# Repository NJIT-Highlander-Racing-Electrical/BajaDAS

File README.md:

# BajaDAS: Readme and Quickstart Guide

## PlatformIO 

1. Software Dependencies:
   - `Visual Studio Code` with `PlatformIO IDE` extension
   - `Git` (if editing)
   - `GitHub Desktop App` (recommended for repository organization)
4. Clone the repository and open the project. If PlatformIO IDE is installed, it should recognize the project and automatically initialize the extension.

## Quick Start

1. Insert a formatted `MicroSD` card into the BajaDAS system.
2. Open the project folder in `Visual Studio Code`.
3. Use the `PlatformIO: Upload` button to load the code onto the microcontroller.
4. Post-race, retrieve the SD card and access the `.csv` files for analysis.

## Troubleshooting

- The main config file is `platformio.ini`.
- Avoid hotswapping MicroSD cards. While the code is set up to automatically detect a card when inserted, the code is very buggy. Always power cycle the system after inserting a new card.

# About BajaDAS
This project was started in 2023 as the first part of our whole-vehicle data acquisition (DAQ) system. It serves as the central data logger, with a few onboard sensors. It is not, however, required by or special on the CAN system.

## System Capabilities
- Data logging via MicroSD card (data is stored in a .csv file)
- Adafruit Ultimate GPS
- Battery Level Sensing
- IMU

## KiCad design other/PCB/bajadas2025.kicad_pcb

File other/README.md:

# BajaDAS: Data Acquisition System for Highlander Racing

BajaDAS is a data acquisition system tailored for the Highlander Racing team's vehicles. It gathers real-time telemetry data, crucial for performance analytics and diagnostics.

## 2025-2026 Changes to Make

* Incorporate this [Adafruit Panel Mount Micro SD Card Extender](https://www.google.com/aclk?sa=l&ai=DChcSEwjj9bOK6cmKAxXBVEcBHVRjHN4YABASGgJxdQ&ae=2&aspm=1&co=1&ase=5&gclid=Cj0KCQiAvbm7BhC5ARIsAFjwNHsn8yJzOILmMZRqH4E_HPufaiggZcexFWYqg4a0y1KrF-u19AfAwZwaAi_wEALw_wcB&sig=AOD64_018L6tCDBYVmc7ekdmUu69rXhYmw&ctype=5&q=&ved=2ahUKEwjsy62K6cmKAxUiFFkFHVE7BFwQww8oAnoECAYQDA&adurl=) for easier use. This will require a waterproof screw on or press fit cover but will make removing the microSD far easier
     * I think we can also just place a microSD card slot for the other end of that panel mount directly to the PCB. It looks like the "reader" we use now just does some voltage regulation and level shifting, but since the ESP32 already uses 3.3V we may be OK without the additional hardware
     * Update the 3D Model and the PCB accordingly for these changes

* Include external pull-up resistors for any input pins on 34, 35, 36, or 39 since these do not have internal pullups

## Features

- **9-DOF Sensor**: Gathers acceleration, magnetic field, gyroscope, and temperature data via the `Adafruit_LSM9DS1` sensor.
- **GPS Integration**: Records GPS data, specifically latitude, longitude, fix status, and satellite count.
- **SD Card Logging**: Logs data to an SD card in CSV format.
- **Serial Logging**: Outputs sensor readings to the serial console for live monitoring.
- **CAN Bus Support**: Receives all incoming vehicle data using a TJA1051T CAN Transceiver.
- **Connection Modularity**: Screw Terminals on DAQ PCB so that additional modules can be connected to the microcontroller in the future
- **Fuel Sensor**: Integrates the fuel sensor and data storage as a part of the DAS

## Hardware Setup

- **Microcontroller**: Designed for Arduino-compatible boards with multiple hardware serial interfaces and SPI capabilities.
- **SD Card**: MicroSD card slot for data logging. Ensure it's formatted correctly.
- **Sensors**: Adafruit LSM9DS1 9-DOF sensor and a GPS module.

## GPS Information

* GPS System that tracks vehicle location (latitude and longitude) as well as reporting other information like time and date

### GPS Design Goals

* CAN-Bus integration with Adafruit Ultimate GPS module reports latitude, longitude, time, and date
* Active antenna mounted to firewall increases reception

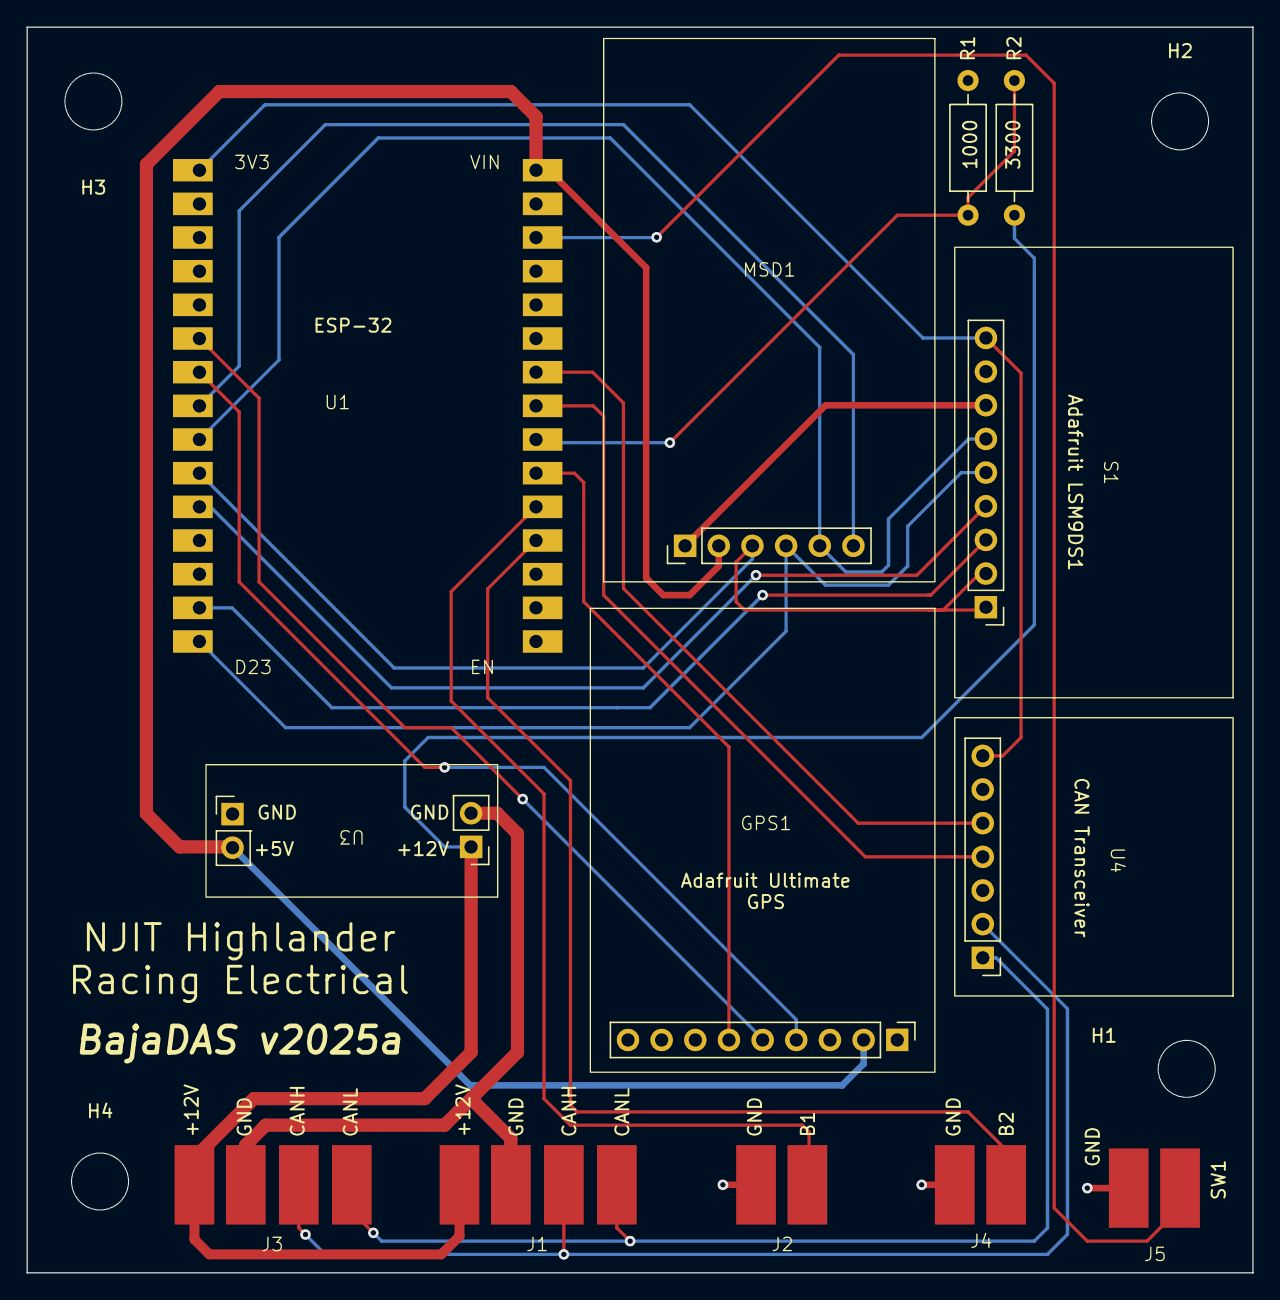
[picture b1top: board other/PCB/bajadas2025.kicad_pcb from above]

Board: 2 copper layers, 92.5 x 94.0 mm, 17 parts (0 on the bottom side), 21 nets.

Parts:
GPS1: Adafruit Ultimate GPS v1
H1, H2, H3, H4: MountingHole; MountingHole_4.3mm_M4
J1: Auxiliary Data/Power Connection; 4pin
J2: Spare Button 1; 2pin
J3: Data/Power Connection; 4pin
J4: Spare Button 2; 2pin
J5: Spare Toggle Switch; 2pin
MSD1: SD Card Reader v1
R1: 1000; R_Axial_DIN0207_L6.3mm_D2.5mm_P10.16mm_Horizontal
R2: 3300; R_Axial_DIN0207_L6.3mm_D2.5mm_P10.16mm_Horizontal
S1: Adafruit LSM9DS1
U1: ESP 32 BAJA
U3: Regulator_v1
U4: CAN Bus Tranceiver v1

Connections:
+3.3V: S1.9 (VIN), U1.1 (3V3), U4.7 (VCC)
+5V: GPS1.2 (VIN), MSD1.2 (VCC), U1.30 (VIN), U3.3 (+5v)
+12V: J1.1, J3.1, R2.1, U3.1 (+12v)
/B1: J2.2, U1.20 (D35)
/B2: J4.2, U1.19 (D34)
/CANH: J1.3, J3.3, U4.2 (CANH)
/CANL: J1.4, J3.4, U4.1 (CANL)
/CRX: U1.24 (D26), U4.5 (RX)
/CS: MSD1.6 (CS), U1.8 (D5)
/CSAG: S1.4 (CSAG), U1.11 (D21)
/CSM: S1.3 (CSM), U1.14 (D22)
/CTX: U1.23 (D25), U4.4 (TX)
/GPS_FIX: GPS1.6 (FIX), U1.21 (D32)
/LOW_BATT: R1.1, R2.2, U1.22 (D33)
/MISO: MSD1.3 (MISO), S1.1 (SDOM), S1.2 (SDOAG), U1.10 (D19)
/MOSI: MSD1.4 (MOSI), S1.5 (SDA), U1.15 (D23)
/RXD: GPS1.5 (TX), U1.6 (RX2)
/SCK: MSD1.5 (SCK), S1.6 (SCL), U1.9 (D18)
/SW1: J5.2, U1.28 (D13)
/TXD: GPS1.4 (RX), U1.7 (TX2)
GND: GPS1.3 (GND), J1.2, J2.1, J3.2, J4.1, J5.1, MSD1.1 (GND), R1.2, S1.7 (GND), U1.2 (GND), U1.29 (GND), U3.2 (GND_IN), U3.4 (GND_OUT), U4.6 (GND)

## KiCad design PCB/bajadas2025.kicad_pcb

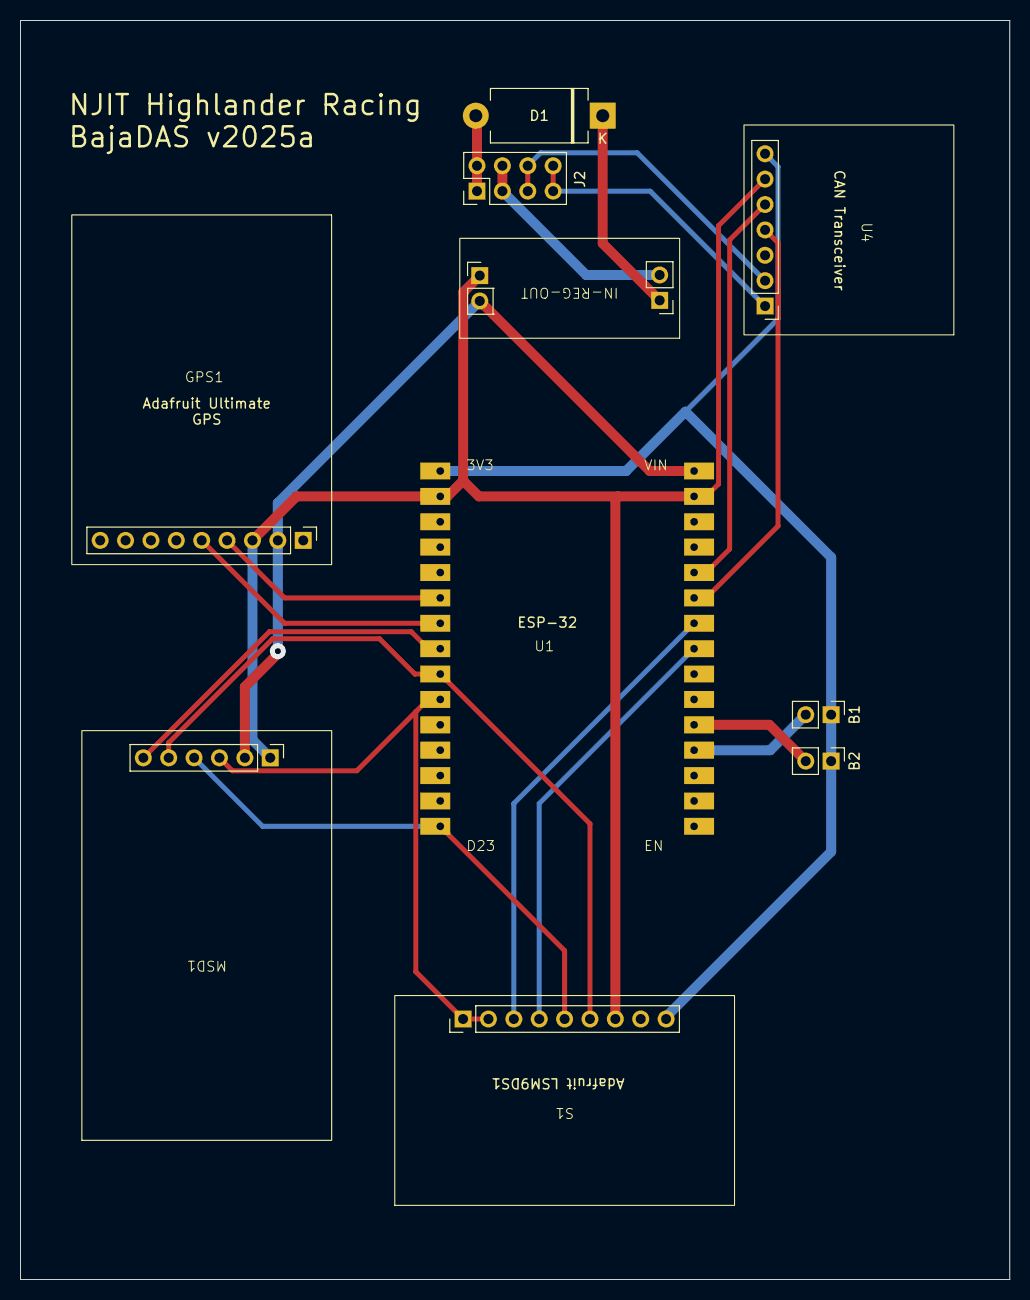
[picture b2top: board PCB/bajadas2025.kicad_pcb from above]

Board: 2 copper layers, 99.0 x 126.0 mm, 10 parts (0 on the bottom side), 20 nets.

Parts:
B1: Spare Button 1; PinHeader_1x02_P2.54mm_Vertical
B2: Spare Button 2; PinHeader_1x02_P2.54mm_Vertical
D1: D_Schottky; D_DO-201_P12.70mm_Horizontal
GPS1: Adafruit Ultimate GPS v1
IN-REG-OUT: Regulator_v1
J2: Data/Power Connection; PinHeader_2x04_P2.54mm_Vertical
MSD1: SD Card Reader v1
S1: Adafruit LSM9DS1
U1: ESP 32 BAJA
U4: CAN Bus Tranceiver v1

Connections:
+3.3V: B1.1, B2.1, S1.9 (VIN), U1.1 (3V3), U4.7 (VCC)
+5V: GPS1.2 (VIN), IN-REG-OUT.3 (+5v), MSD1.2 (VCC), U1.30 (VIN)
+12V: D1.1 (K), IN-REG-OUT.1 (+12v)
/B1: B1.2, U1.19 (D34)
/B2: B2.2, U1.20 (D35)
/CANH: J2.5, J2.6, U4.2 (CANH)
/CANL: J2.7, J2.8, U4.1 (CANL)
/CRX: U1.26 (D14), U4.5 (RX)
/CS: MSD1.6 (CS), U1.8 (D5)
/CSAG: S1.4 (CSAG), U1.23 (D25)
/CSM: S1.3 (CSM), U1.24 (D26)
/CTX: U1.25 (D27), U4.4 (TX)
/MISO: MSD1.3 (MISO), S1.1 (SDOM), S1.2 (SDOAG), U1.10 (D19)
/MOSI: MSD1.4 (MOSI), S1.5 (SDA), U1.15 (D23)
/RXD: GPS1.4 (RX), U1.6 (RX2)
/SCK: MSD1.5 (SCK), S1.6 (SCL), U1.9 (D18)
/TXD: GPS1.5 (TX), U1.7 (TX2)
GND: GPS1.3 (GND), IN-REG-OUT.4 (GND_OUT), MSD1.1 (GND), S1.7 (GND), U1.2 (GND), U1.29 (GND), U4.6 (GND)
GND1: IN-REG-OUT.2 (GND_IN), J2.3, J2.4
unnamed: D1.2 (A), J2.1, J2.2

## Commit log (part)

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2023-09-28 Added entire project to repository
2023-09-28 Removed venv folder
2023-09-28 typo README.md
2023-09-29 Added NMEA GPS data parsing and logging
2024-02-17 Minor changes
    -More descriptive comments for how to wire LSM9DS1 to new ESP32 board (devkit v1)
    -Changed failure/success messages in serial monitor to look better (imo)
    -Added a success message for the GPS module
    Coding changes are minor, but a whole new breadboard layout was started.
2024-02-17 Delete main.cpp
    added to wrong place
2024-04-07 lots of new stuff
2024-04-13 code update
    this works mostly.
2024-04-21 Rename DAQ Housing.step to 3D Models/DAQ Housing.step
2024-04-21 Rename IMG_1247.JPG to Photos/IMG_1247.JPG
2024-05-14 moving 2023-2024 files to archive
2024-05-14 adding default files and folders
2024-05-16 updated with convert GPS data to decimal degrees
2024-09-30 Fix some transceiver issues
2024-09-30 Uploaded to wrong spot
2024-09-30 Fix some transceiver issues (part 2)
2024-10-06 Update main.cpp to save singular wheel speed sensor data
2024-10-18 Update loop delay to increase polling rate
2024-10-18 Create Library123
2024-10-20 Update Software Folder Layout
2024-10-24 Add another %i for SD card logging for wheel speed
2024-11-09 Update main.cpp
    ooga booga the code is change-ooga
2024-11-15 Add first version of DAS enclosure
2024-11-17 Update Enclosure
2024-12-15 Create dummyfile
2024-12-15 Initial PCB Commit
2024-12-15 Various Modifications
    Update Data/Power Connection to use pads
    Update spare buttons to use pads
    Update spare buttons to be tied to ground (to use internal pullup)
    Fix Ultimate GPS to use GPS_RX->ESP32_TX and GPS_TX-ESP32_RX
    Connect GPS_FIX to an arbitrary GPIO input pin in case we want to use it in the future
    Add pads for toggle switch
2024-12-15 Update 3D Models for new PCB
2024-12-29 Add working test sketch for adafruit ultimate gps
2024-12-29 Update 3D Model
2025-01-03 Add welding alignment bracket to 3D Model
2025-01-03 Aesthetic improvements for u.FL Adapter and CAN Transceiver
2025-01-27 reorganization
2025-01-27 reorg + push new changes
2025-01-29 Rename "other" folder
2025-02-15 Revert "delete old files"
    This reverts commit e5d0144e9f0b5f0a34804afeb63550d6ea13255a.
2025-02-15 v2 creation
    Created a new platformio project and set up easier editing of repository
2025-02-15 test
2025-02-15 undo test
2025-02-15 gitignore changes
    .gitignore no longer keeps .pio/build out of the repository
2025-02-15 Revert "gitignore changes"
    This reverts commit d1a1e7bd7e15f80c893911629e9aca5583579c36.
2025-02-15 readme update
2025-02-16 .gitignore changes
2025-02-16 readding misc. files
2025-02-18 removed old can code
2025-02-22 changed platformio.ini to use correct can branch
2025-02-22 Removed deprecated can and offset code
2025-02-22 same as last
2025-04-05 Several updates
2025-04-05 Time now prints with \t instead of colon
    This helps so that when we replace the \t with a , for SerialStudio, the parsing does nto get messed up
2025-04-05 Fix order of message printing for serial studio
2025-04-05 Increase # of decimal places when serial printing GPS
2025-04-05 Update (GPS heading and velocity and altitude stuff)
2025-04-05 Up Serial baud rate to 460800 (so we spend less time processing serial print requests)
2025-04-06 Update GPS to 10Hz rate
2025-04-06 Small updates
2025-04-06 Final updates for day
2025-04-12 Add code for brake pressure sensors
2025-04-13 Latest JSON for SerialStudio
2025-04-13 Fix project name title
2025-04-13 Remove wait for Serial to be opened
2025-04-13 Fix date not being parsed in parseGPRMC
2025-04-13 Fix date/month/year strings not being updated for file path descriptive
2025-04-13 dateString vs dayString mixup
2025-04-19 Update 3D models
2025-04-19 Rename other/2024-2025 DAS Enclosure v45.step to other/3D Models/2024-2025 DAS Enclosure v45.step
2025-04-22 Add back while(!Serial)
    This is necessary not for waiting for the user to open the serial monitor, but for the serial monitor to properly initialize
2025-04-25 Serial.begin issues again
    It looks like after some short research that while(!Serial) does not work on ESP32's? So just testing to see if a delay is sufficient
2025-05-02 Change wheel speed units from RPM to MPH
2025-05-02 Update wheel rpm to MPH and change units for logging to SD
2025-05-02 Fix bug where date was showing as 2080 in descriptive log file
2025-05-03 comment out timezone and hard code, GPZDA does not give local timezone
    https://docs.novatel.com/OEM7/Content/Logs/GPZDA.htm
2025-05-03 Nevermind, hour was hardcoded to -4, fixed that to use timezone offset
2025-05-03 GPZDA for time zone wasn't even being executed
2025-05-03 Last update (hopefully) see desc
    It looks like GPZDA indeed is not able to get local time zone offsets. So just going with hard coded, and removed all GPZDA references. Will test tomorrow
2025-05-03 Fix sign of timezone correction
2025-05-10 Go back to EDT from marana time
2025-06-12 Fix separation character for serial monitor printing
2025-06-13 Update ranges for wheel speed and battery voltage
2025-06-14 (TESTING FILE) plus fixes
    Added a testing line to see if GPS is actually printing 10 Hz (looks slower in serial studio replay)
    Updated all Serial.prints for SerialStudio and Serial Monitor to only print 3 decimal places. Hopefully this will fix the issue with data shifts in the CSVs (assuming it is coming from printing long 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
2025-06-14 Delay after baud rate change to maybe fix it
2025-06-14 Successfully fixed GPS not parsing every 100ms (10Hz
2025-06-14 Fix wheel displacement range
2025-08-02 Fix the shock position data incidces
2025-09-06 update ini to use the main branch of bajacan
2025-09-06 removed extraneous files
2025-09-06 Remove wheel states from SD logging and SerialStudio/Serial Logging
2025-09-06 Fix printing after removing wheel states
2025-09-06 Add Data flag to serial studio display
2025-09-06 Increase serial print rate to 460800
    this should allow to faster and more prints to serial monitor. also allows for more saves to SD card. That might be our bottleneck for SD logging rate
2025-09-07 Several updates, see desc
    These updates are to increase the max possible polling rate. Claude rewrote code to have faster SD logging (keeps file open and flushes every so often to not lose tons of data on power off). I rewrot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
2025-10-24 Update program to include CVT belt temp
2025-10-24 Update accelerometer to 16g
2025-10-25 Fix printing
2025-10-25 Fix incorrect printing order
    Belt temp was added in two different spots so serial studio printing was not wokring right for SD vs Serial realtime
2026-05-07 Change monitor_speed to 460800
    was 115200
2026-05-07 SD logging now always on, formatting
